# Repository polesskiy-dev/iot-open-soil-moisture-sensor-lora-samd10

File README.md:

# IoT Soil Moisture Sensor

### Open source, low power, cost-effective, 10 years from 1 LiSOCl2 battery. LoRa communication channel. Supports 2 probes functionality for multi-depth sensoring.

### Based on [Microchip (Atmel) SAMD10 ](https://ww1.microchip.com/downloads/en/DeviceDoc/Atmel-42242-SAM-D10_Datasheet.pdf) chip: ~1.5$, 32bit Cortex M0+

## Features

- LoRa communication
- LiSOCl2 7.7A 26500 battery
- RTC clock
- 2 I2C SHTxx Senserion sensors
- Battery self-measure

## Schematics

## PCB

## PCB Renders

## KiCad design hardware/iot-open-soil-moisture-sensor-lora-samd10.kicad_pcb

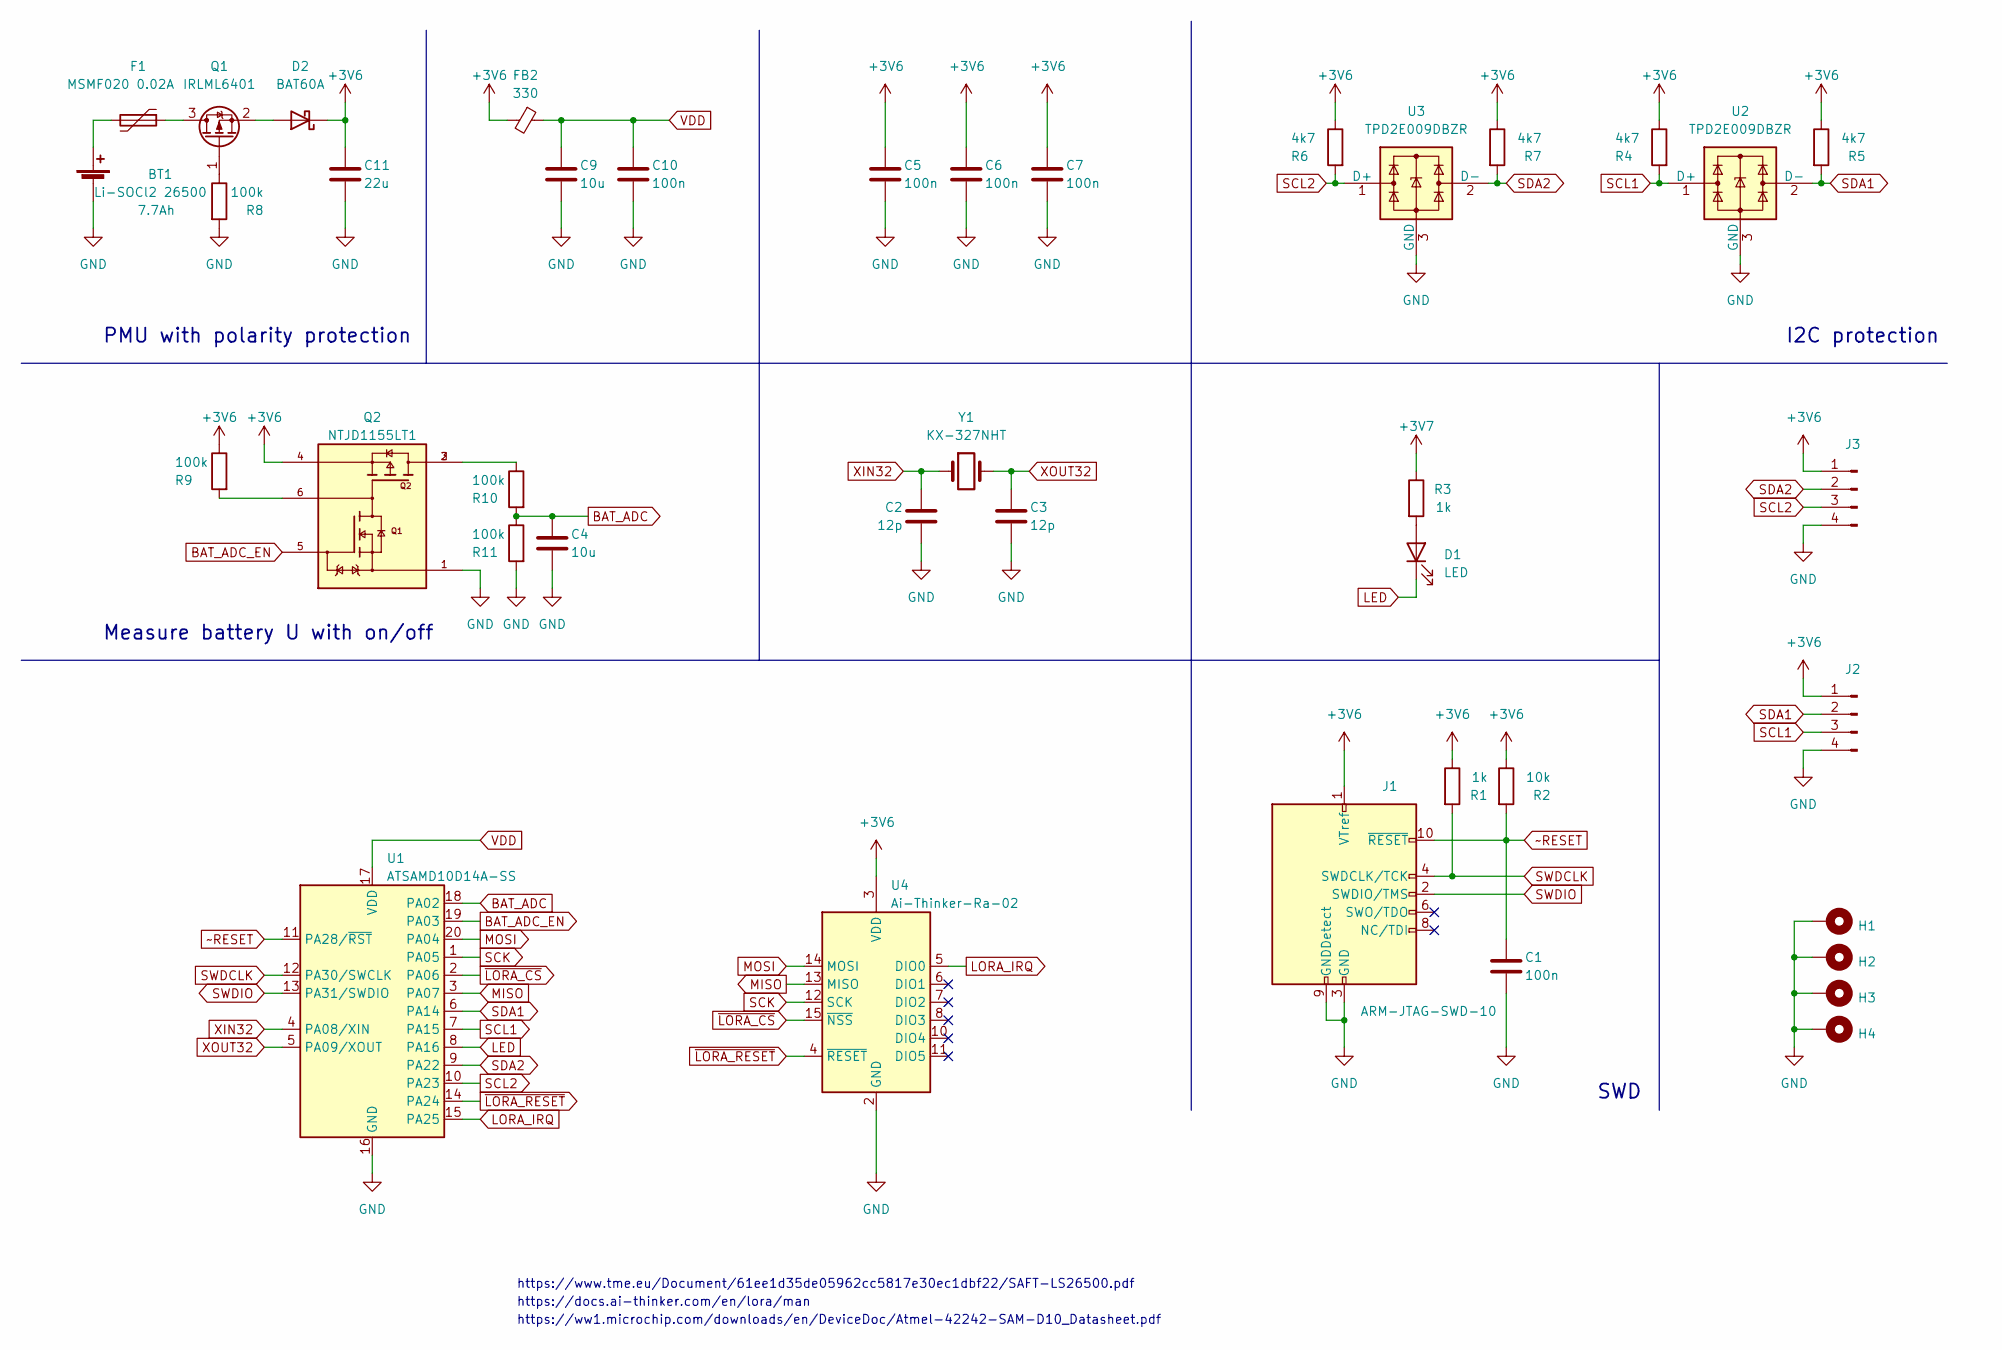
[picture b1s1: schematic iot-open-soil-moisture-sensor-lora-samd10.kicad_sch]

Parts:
BT1: Li-SOCl2 26500; BAT-26500
C1, C5, C6, C7, C10: 100n; C_0805_2012Metric_Pad1.18x1.45mm_HandSolder
C2, C3: 12p; C_0805_2012Metric_Pad1.18x1.45mm_HandSolder
C4, C9: 10u; C_0805_2012Metric_Pad1.18x1.45mm_HandSolder
C11: 22u; C_1206_3216Metric_Pad1.33x1.80mm_HandSolder
D1: LED; LED_0805_2012Metric_Pad1.15x1.40mm_HandSolder
D2: BAT60A; D_SOD-323_HandSoldering
F1: MSMF020 0.02A; C_1812_4532Metric_Pad1.57x3.40mm_HandSolder
FB2: 330; R_0805_2012Metric_Pad1.20x1.40mm_HandSolder
H1, H2, H3, H4: MountingHole_Pad; MountingHole_3.2mm_M3_Pad_Via
J1: ARM-JTAG-SWD-10; PinHeader_2x05_P2.54mm_Vertical
J2, J3: Conn_01x04_Pin; SolderWire-0.1sqmm_1x04_P3.6mm_D0.4mm_OD1mm_Relief
Q1: IRLML6401; SOT-23
Q2: NTJD1155LT1; SOT-363_SC-70-6_Handsoldering; PARTREV Rev. 6
R1, R3: 1k; R_0805_2012Metric_Pad1.20x1.40mm_HandSolder
R2: 10k; R_0805_2012Metric_Pad1.20x1.40mm_HandSolder
R4, R5, R6, R7: 4k7; R_0805_2012Metric_Pad1.20x1.40mm_HandSolder
R8, R9, R10, R11: 100k; R_0805_2012Metric_Pad1.20x1.40mm_HandSolder
U1: ATSAMD10D14A-SS; SOIC-20W_7.5x12.8mm_P1.27mm
U2, U3: TPD2E009DBZR; SOT-23
U4: Ai-Thinker-Ra-02; Ai-Thinker-Ra-01-LoRa
Y1: KX-327NHT; Crystal_SMD_EuroQuartz_EQ161-2Pin_3.2x1.5mm_HandSoldering

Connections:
BAT_ADC: C4.1, R10.2, R11.1; also elsewhere on the board
BAT_ADC_EN: Q2.5, U1.19 (PA03); also elsewhere on the board
GND: BT1.2 (-), C1.2, C2.2, C3.2, C4.2, C5.2, C6.2, C7.2, C9.2, C10.2, C11.2, H1.1, H2.1, H3.1, H4.1, J2.4, J3.4, Q2.1, R8.2, R11.2, U2.3 (GND), U3.3 (GND); also elsewhere on the board
LED: D1.1 (K); also elsewhere on the board
unnamed: BT1.1 (+), F1.2
unnamed: D1.2 (A), R3.2
unnamed: D2.2 (A), Q1.2 (S)
unnamed: J1.2 (SWDIO/TMS), U1.13 (PA31/SWDIO)
unnamed: F1.1, Q1.3 (D)
unnamed: Q1.1 (G), R8.1
unnamed: Q2.2, Q2.3, R10.1
unnamed: Q2.6, R9.2
unnamed: U1.1 (PA05), U4.12 (SCK)
unnamed: U1.2 (PA06), U4.15 (~NSS)
unnamed: U1.3 (PA07), U4.13 (MISO)
unnamed: U1.14 (PA24), U4.4 (~RESET)
unnamed: U1.15 (PA25), U4.5 (DIO0)
unnamed: U1.20 (PA04), U4.14 (MOSI)
SCL1: J2.3, R4.2, U2.1 (D+); also elsewhere on the board
SCL2: J3.3, R6.2, U3.1 (D+); also elsewhere on the board
SDA1: J2.2, R5.2, U2.2 (D-); also elsewhere on the board
SDA2: J3.2, R7.2, U3.2 (D-); also elsewhere on the board
SWDCLK: R1.2; also elsewhere on the board
VDD: C9.1, C10.1, FB2.1; also elsewhere on the board
XIN32: C2.1, Y1.1; also elsewhere on the board
XOUT32: C3.1, Y1.2; also elsewhere on the board
~RESET: C1.1, R2.2; also elsewhere on the board

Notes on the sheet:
https://ww1.microchip.com/downloads/en/DeviceDoc/Atmel-42242-SAM-D10_Datasheet.pdf
PMU with polarity protection
SWD
I2C protection
https://www.tme.eu/Document/61ee1d35de05962cc5817e30ec1dbf22/SAFT-LS26500.pdf
https://docs.ai-thinker.com/en/lora/man
Measure battery U with on/off

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
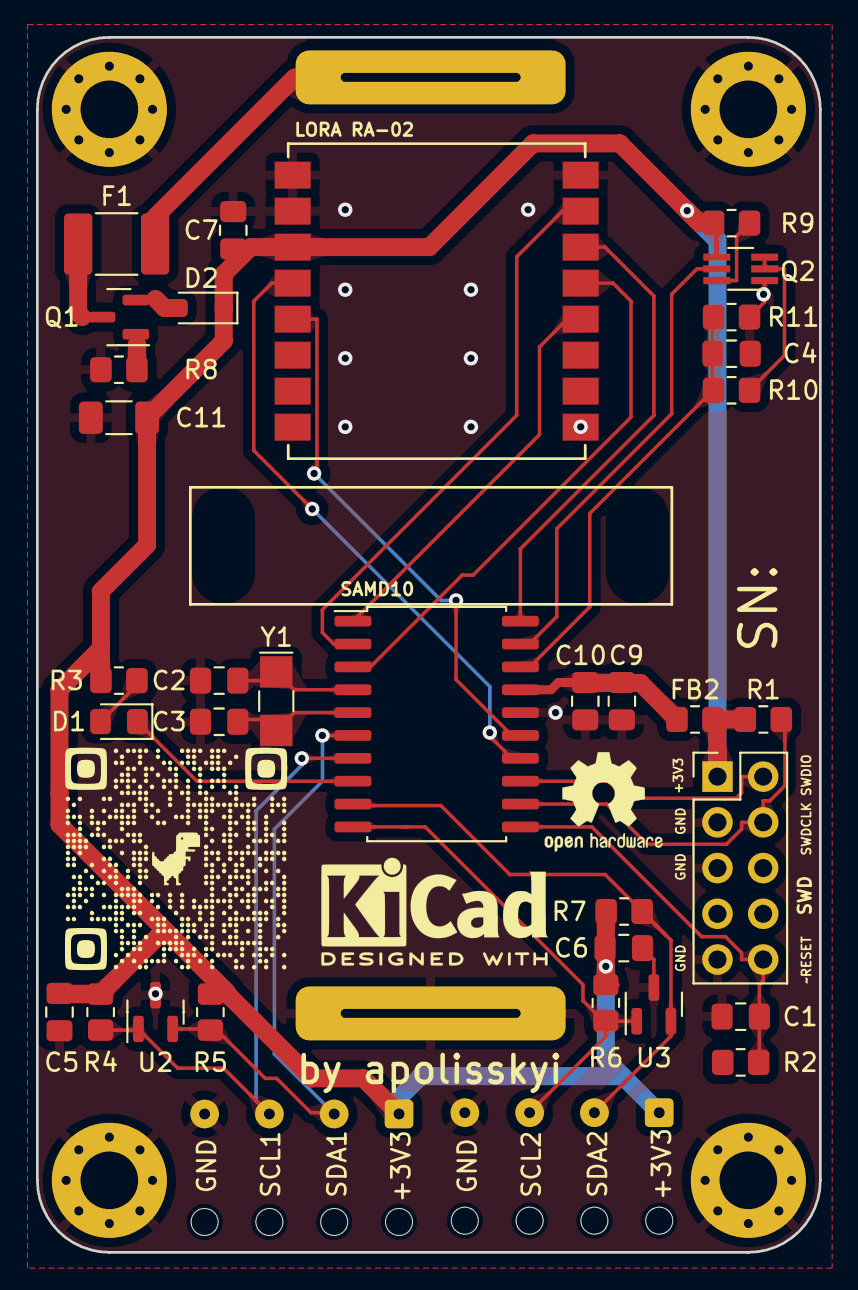
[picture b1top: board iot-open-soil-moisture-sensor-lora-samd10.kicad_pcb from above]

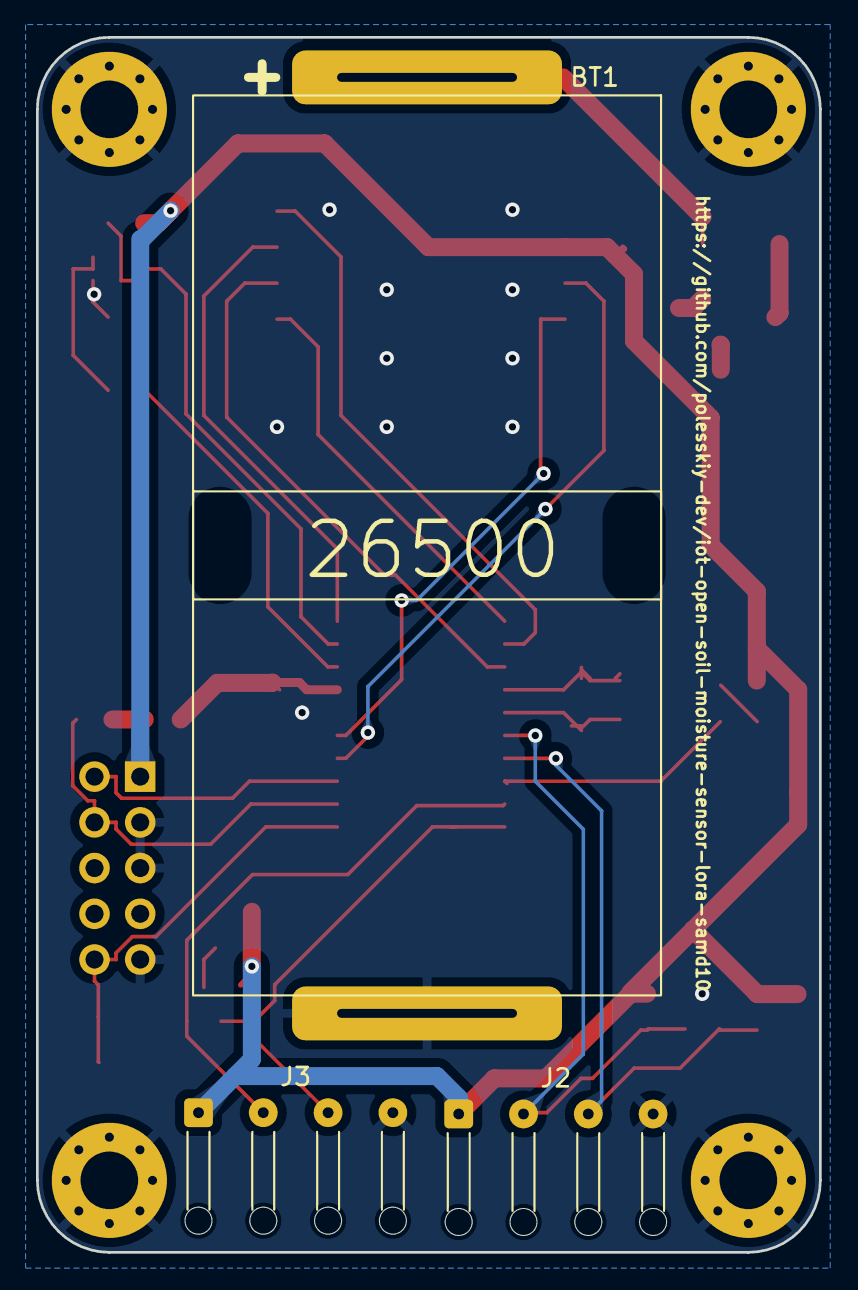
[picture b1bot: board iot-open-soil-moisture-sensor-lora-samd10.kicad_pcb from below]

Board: 2 copper layers, 43.5 x 67.5 mm, 40 parts (3 on the bottom side), 28 nets.

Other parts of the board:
LORA RA-02: Ai-Thinker-Ra-02; Ai-Thinker-Ra-01-LoRa
SAMD10: ATSAMD10D14A-SS; SOIC-20W_7.5x12.8mm_P1.27mm
SWD: ARM-JTAG-SWD-10; PinHeader_2x05_P2.54mm_Vertical

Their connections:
BAT_ADC: SAMD10.18 (PA02); also elsewhere on the board
BAT_ADC_EN: SAMD10.19 (PA03); also elsewhere on the board
GND: LORA RA-02.1 (GND), LORA RA-02.2 (GND), LORA RA-02.9 (GND), LORA RA-02.16 (GND), SAMD10.16 (GND), SWD.3 (GND), SWD.5 (GND), SWD.9 (GNDDetect); also elsewhere on the board
LED: SAMD10.8 (PA16); also elsewhere on the board
LORA_IRQ: LORA RA-02.5 (DIO0), SAMD10.15 (PA25)
MISO: LORA RA-02.13 (MISO), SAMD10.3 (PA07)
MOSI: LORA RA-02.14 (MOSI), SAMD10.20 (PA04)
SCK: LORA RA-02.12 (SCK), SAMD10.1 (PA05)
SCL1: SAMD10.7 (PA15); also elsewhere on the board
SCL2: SAMD10.10 (PA23); also elsewhere on the board
SDA1: SAMD10.6 (PA14); also elsewhere on the board
SDA2: SAMD10.9 (PA22); also elsewhere on the board
SWDCLK: SAMD10.12 (PA30/SWCLK), SWD.4 (SWDCLK/TCK); also elsewhere on the board
SWDIO: SAMD10.13 (PA31/SWDIO), SWD.2 (SWDIO/TMS)
VDD: SAMD10.17 (VDD); also elsewhere on the board
XIN32: SAMD10.4 (PA08/XIN); also elsewhere on the board
XOUT32: SAMD10.5 (PA09/XOUT); also elsewhere on the board
~RESET: SAMD10.11 (PA28/~RST), SWD.10 (~RESET); also elsewhere on the board
~LORA_CS: LORA RA-02.15 (~NSS), SAMD10.2 (PA06)
~LORA_RESET: LORA RA-02.4 (~RESET), SAMD10.14 (PA24)

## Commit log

2023-02-19 create schematics first revision
2023-02-20 create PCB first revision
2023-02-22 add PCB signs
2023-02-22 add initial documentation
